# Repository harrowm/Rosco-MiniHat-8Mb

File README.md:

# Rosco-Minihat-8Mb
A 8Mb memory hat for the rosco_m68k SBC

This design has not been built or tested.  The use of 2Mb chips means moving to 3.3v with buffer chips and a voltage regulator.  This is really too much to cram into a "hat" type board.  When I find the time I will redesign as a normal board as I have the parts on hand ..

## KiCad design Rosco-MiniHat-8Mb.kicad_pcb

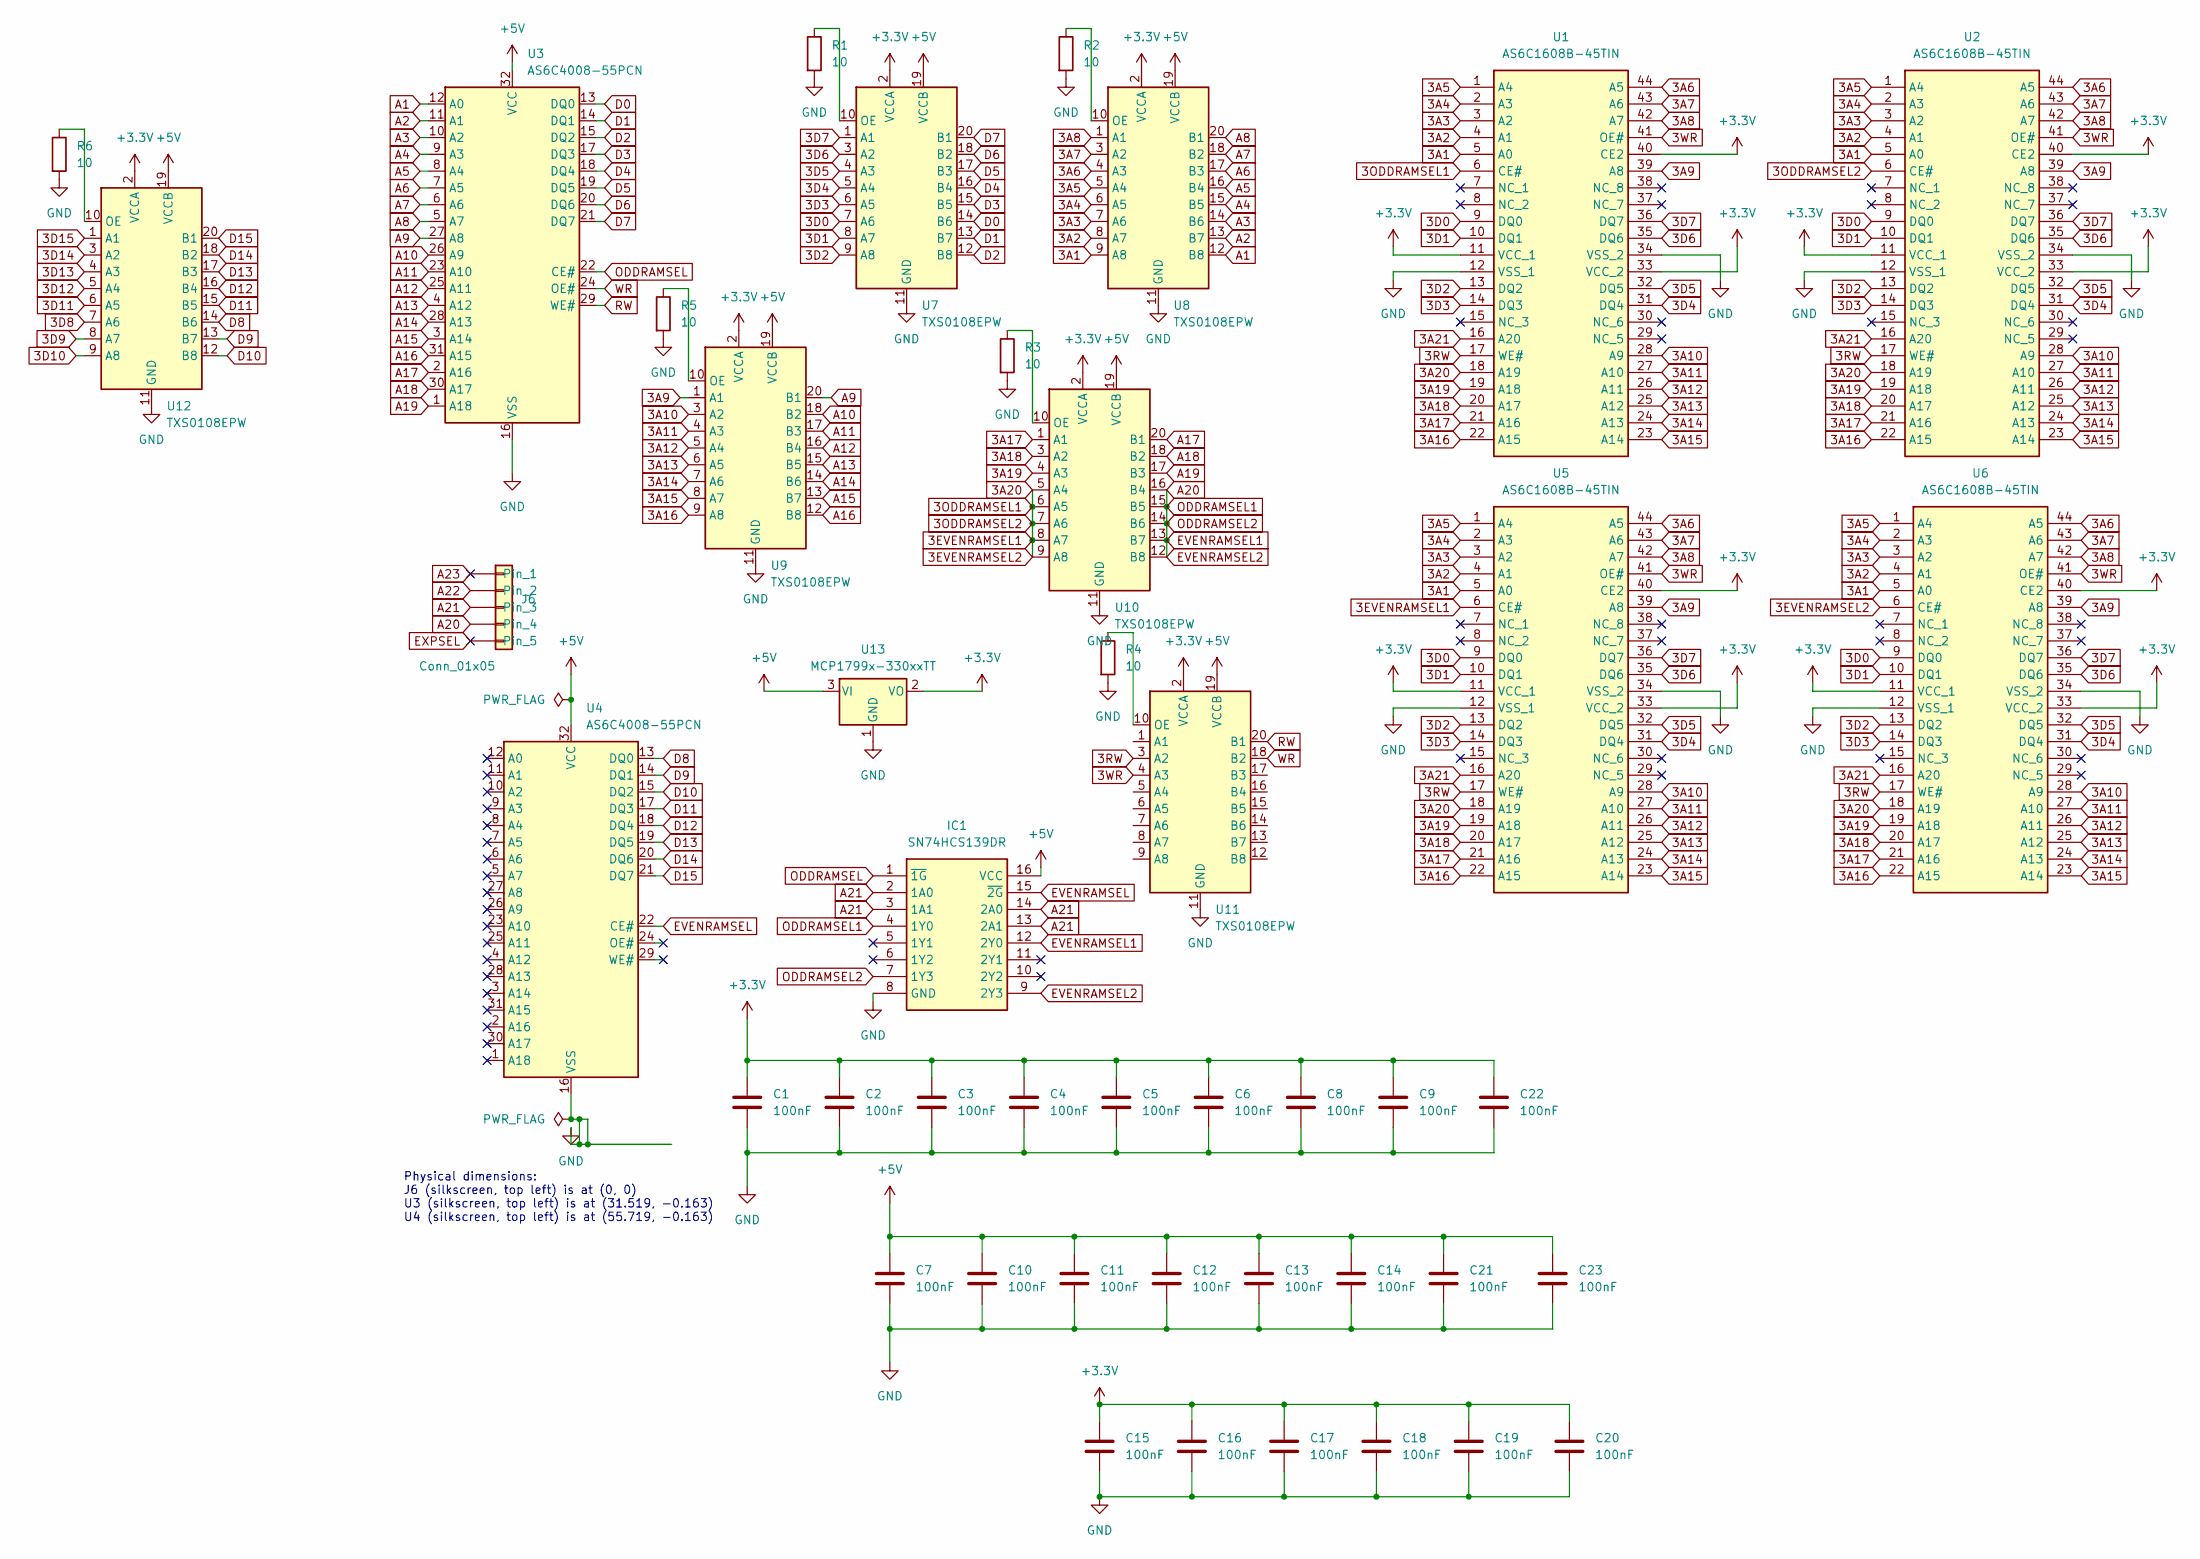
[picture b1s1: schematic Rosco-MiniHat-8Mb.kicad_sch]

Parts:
C1, C2, C3, C4, C5, C6, C7, C8, C9, C10, C11, C12, C13, C14, C15, C16, C17, C18, C19, C20, C21, C22, C23: 100nF; C_0805_2012Metric_Pad1.18x1.45mm_HandSolder
IC1: SN74HCS139DR; SOIC-16_3.9x9.9mm_P1.27mm; Mouser Part Number 595-SN74HCS139DR
J6: Conn_01x05; PinHeader_1x05_P2.54mm_Vertical
R1, R2, R3, R4, R5, R6: 10; R_0805_2012Metric_Pad1.20x1.40mm_HandSolder
U1, U2, U5, U6: AS6C1608B-45TIN; TSOP-II-44_10.16x18.41mm_P0.8mm; Manufacturer_Part_Number AS6C1608B-45TIN; Mouser Part Number 913-AS6C1608B-45TIN
U3, U4: AS6C4008-55PCN; DIP-32_W15.24mm
U7, U8, U9, U10, U11, U12: TXS0108EPW; TSSOP-20_4.4x6.5mm_P0.65mm
U13: MCP1799x-330xxTT; SOT-23

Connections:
3A1: U1.5 (A0), U2.5 (A0), U5.5 (A0), U6.5 (A0), U8.9 (A8)
3A2: U1.4 (A1), U2.4 (A1), U5.4 (A1), U6.4 (A1), U8.8 (A7)
3A3: U1.3 (A2), U2.3 (A2), U5.3 (A2), U6.3 (A2), U8.7 (A6)
3A4: U1.2 (A3), U2.2 (A3), U5.2 (A3), U6.2 (A3), U8.6 (A5)
3A5: U1.1 (A4), U2.1 (A4), U5.1 (A4), U6.1 (A4), U8.5 (A4)
3A6: U1.44 (A5), U2.44 (A5), U5.44 (A5), U6.44 (A5), U8.4 (A3)
3A7: U1.43 (A6), U2.43 (A6), U5.43 (A6), U6.43 (A6), U8.3 (A2)
3A8: U1.42 (A7), U2.42 (A7), U5.42 (A7), U6.42 (A7), U8.1 (A1)
3A9: U1.39 (A8), U2.39 (A8), U5.39 (A8), U6.39 (A8), U9.1 (A1)
3A10: U1.28 (A9), U2.28 (A9), U5.28 (A9), U6.28 (A9), U9.3 (A2)
3A11: U1.27 (A10), U2.27 (A10), U5.27 (A10), U6.27 (A10), U9.4 (A3)
3A12: U1.26 (A11), U2.26 (A11), U5.26 (A11), U6.26 (A11), U9.5 (A4)
3A13: U1.25 (A12), U2.25 (A12), U5.25 (A12), U6.25 (A12), U9.6 (A5)
3A14: U1.24 (A13), U2.24 (A13), U5.24 (A13), U6.24 (A13), U9.7 (A6)
3A15: U1.23 (A14), U2.23 (A14), U5.23 (A14), U6.23 (A14), U9.8 (A7)
3A16: U1.22 (A15), U2.22 (A15), U5.22 (A15), U6.22 (A15), U9.9 (A8)
3A17: U1.21 (A16), U2.21 (A16), U5.21 (A16), U6.21 (A16), U10.1 (A1)
3A18: U1.20 (A17), U2.20 (A17), U5.20 (A17), U6.20 (A17), U10.3 (A2)
3A19: U1.19 (A18), U2.19 (A18), U5.19 (A18), U6.19 (A18), U10.4 (A3)
3A20: U1.6 (CE#), U1.18 (A19), U2.6 (CE#), U2.18 (A19), U5.6 (CE#), U5.18 (A19), U6.6 (CE#), U6.18 (A19), U10.5 (A4), U10.6 (A5), U10.7 (A6), U10.8 (A7), U10.9 (A8)
3A21: U1.16 (A20), U2.16 (A20), U5.16 (A20), U6.16 (A20)
3D0: U1.9 (DQ0), U2.9 (DQ0), U5.9 (DQ0), U6.9 (DQ0), U7.7 (A6)
3D1: U1.10 (DQ1), U2.10 (DQ1), U5.10 (DQ1), U6.10 (DQ1), U7.8 (A7)
3D2: U1.13 (DQ2), U2.13 (DQ2), U5.13 (DQ2), U6.13 (DQ2), U7.9 (A8)
3D3: U1.14 (DQ3), U2.14 (DQ3), U5.14 (DQ3), U6.14 (DQ3), U7.6 (A5)
3D4: U1.31 (DQ4), U2.31 (DQ4), U5.31 (DQ4), U6.31 (DQ4), U7.5 (A4)
3D5: U1.32 (DQ5), U2.32 (DQ5), U5.32 (DQ5), U6.32 (DQ5), U7.4 (A3)
3D6: U1.35 (DQ6), U2.35 (DQ6), U5.35 (DQ6), U6.35 (DQ6), U7.3 (A2)
3D7: U1.36 (DQ7), U2.36 (DQ7), U5.36 (DQ7), U6.36 (DQ7), U7.1 (A1)
3D8: U12.7 (A6)
3D9: U12.8 (A7)
3D10: U12.9 (A8)
3D11: U12.6 (A5)
3D12: U12.5 (A4)
3D13: U12.4 (A3)
3D14: U12.3 (A2)
3D15: U12.1 (A1)
3RW: U1.17 (WE#), U2.17 (WE#), U5.17 (WE#), U6.17 (WE#), U11.3 (A2)
3WR: U1.41 (OE#), U2.41 (OE#), U5.41 (OE#), U6.41 (OE#), U11.4 (A3)
+3.3V: C1.1, C2.1, C3.1, C4.1, C5.1, C6.1, C8.1, C9.1, C15.1, C16.1, C17.1, C18.1, C19.1, C20.1, C22.1, U1.11 (VCC_1), U1.33 (VCC_2), U1.40 (CE2), U2.11 (VCC_1), U2.33 (VCC_2), U2.40 (CE2), U5.11 (VCC_1), U5.33 (VCC_2), U5.40 (CE2), U6.11 (VCC_1), U6.33 (VCC_2), U6.40 (CE2), U7.2 (VCCA), U8.2 (VCCA), U9.2 (VCCA), U10.2 (VCCA), U11.2 (VCCA), U12.2 (VCCA), U13.2 (VO)
+5V: C7.1, C10.1, C11.1, C12.1, C13.1, C14.1, C21.1, C23.1, IC1.16 (VCC), U3.32 (VCC), U4.32 (VCC), U7.19 (VCCB), U8.19 (VCCB), U9.19 (VCCB), U10.19 (VCCB), U11.19 (VCCB), U12.19 (VCCB), U13.3 (VI)
A1: U3.12 (A0), U8.12 (B8)
A2: U3.11 (A1), U8.13 (B7)
A3: U3.10 (A2), U8.14 (B6)
A4: U3.9 (A3), U8.15 (B5)
A5: U3.8 (A4), U8.16 (B4)
A6: U3.7 (A5), U8.17 (B3)
A7: U3.6 (A6), U8.18 (B2)
A8: U3.5 (A7), U8.20 (B1)
A9: U3.27 (A8), U9.20 (B1)
A10: U3.26 (A9), U9.18 (B2)
A11: U3.23 (A10), U9.17 (B3)
A12: U3.25 (A11), U9.16 (B4)
A13: U3.4 (A12), U9.15 (B5)
A14: U3.28 (A13), U9.14 (B6)
A15: U3.3 (A14), U9.13 (B7)
A16: U3.31 (A15), U9.12 (B8)
A17: U3.2 (A16), U10.20 (B1)
A18: U3.30 (A17), U10.18 (B2)
A19: U3.1 (A18), U10.17 (B3)
A20: IC1.4 (1Y0), IC1.7 (1Y3), IC1.9 (2Y3), IC1.12 (2Y0), J6.4, U10.12 (B8), U10.13 (B7), U10.14 (B6), U10.15 (B5), U10.16 (B4)
A21: IC1.2 (1A0), IC1.3 (1A1), IC1.13 (2A1), IC1.14 (2A0), J6.3
A22: J6.2
A23: J6.1
D0: U3.13 (DQ0), U7.14 (B6)
D1: U3.14 (DQ1), U7.13 (B7)
D2: U3.15 (DQ2), U7.12 (B8)
D3: U3.17 (DQ3), U7.15 (B5)
D4: U3.18 (DQ4), U7.16 (B4)
D5: U3.19 (DQ5), U7.17 (B3)
D6: U3.20 (DQ6), U7.18 (B2)
D7: U3.21 (DQ7), U7.20 (B1)
D8: U4.13 (DQ0), U12.14 (B6)
D9: U4.14 (DQ1), U12.13 (B7)
D10: U4.15 (DQ2), U12.12 (B8)
D11: U4.17 (DQ3), U12.15 (B5)
D12: U4.18 (DQ4), U12.16 (B4)
D13: U4.19 (DQ5), U12.17 (B3)
D14: U4.20 (DQ6), U12.18 (B2)
D15: U4.21 (DQ7), U12.20 (B1)
EVENRAMSEL: IC1.15 (~2G), U4.22 (CE#)
EXPSEL: J6.5
GND: C1.2, C2.2, C3.2, C4.2, C5.2, C6.2, C7.2, C8.2, C9.2, C10.2, C11.2, C12.2, C13.2, C14.2, C15.2, C16.2, C17.2, C18.2, C19.2, C20.2, C21.2, C22.2, C23.2, IC1.8 (GND), R1.2, R2.2, R3.2, R4.2, R5.2, R6.2, U1.12 (VSS_1), U1.34 (VSS_2), U2.12 (VSS_1), U2.34 (VSS_2), U3.16 (VSS), U4.16 (VSS), U5.12 (VSS_1), U5.34 (VSS_2), U6.12 (VSS_1), U6.34 (VSS_2), U7.11 (GND), U8.11 (GND), U9.11 (GND), U10.11 (GND), U11.11 (GND), U12.11 (GND), U13.1 (GND)
unnamed: R1.1, U7.10 (OE)
unnamed: R2.1, U8.10 (OE)
unnamed: R5.1, U9.10 (OE)
unnamed: R3.1, U10.10 (OE)
unnamed: R4.1, U11.10 (OE)
unnamed: R6.1, U12.10 (OE)
ODDRAMSEL: IC1.1 (~1G), U3.22 (CE#)
RW: U3.29 (WE#), U11.20 (B1)
WR: U3.24 (OE#), U11.18 (B2)

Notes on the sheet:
Physical dimensions: J6 (silkscreen, top left) is at (0, 0) U3 (silkscreen, top left) is at (31.519, -0.163) U4 (silkscreen, top left) is at (55.719, -0.163)

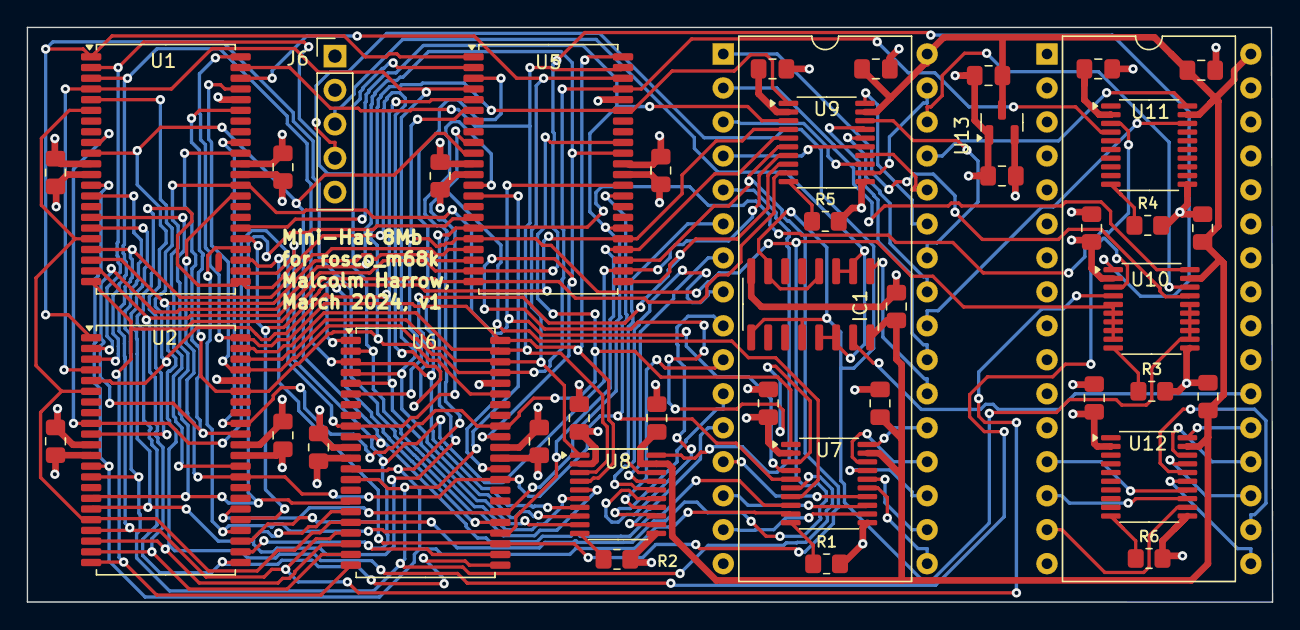
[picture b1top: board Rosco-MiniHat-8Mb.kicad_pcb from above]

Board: 4 copper layers, 93.1 x 43.0 mm, 44 parts (0 on the bottom side), 81 nets.

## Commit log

2025-03-13 Tidy up to mothball
